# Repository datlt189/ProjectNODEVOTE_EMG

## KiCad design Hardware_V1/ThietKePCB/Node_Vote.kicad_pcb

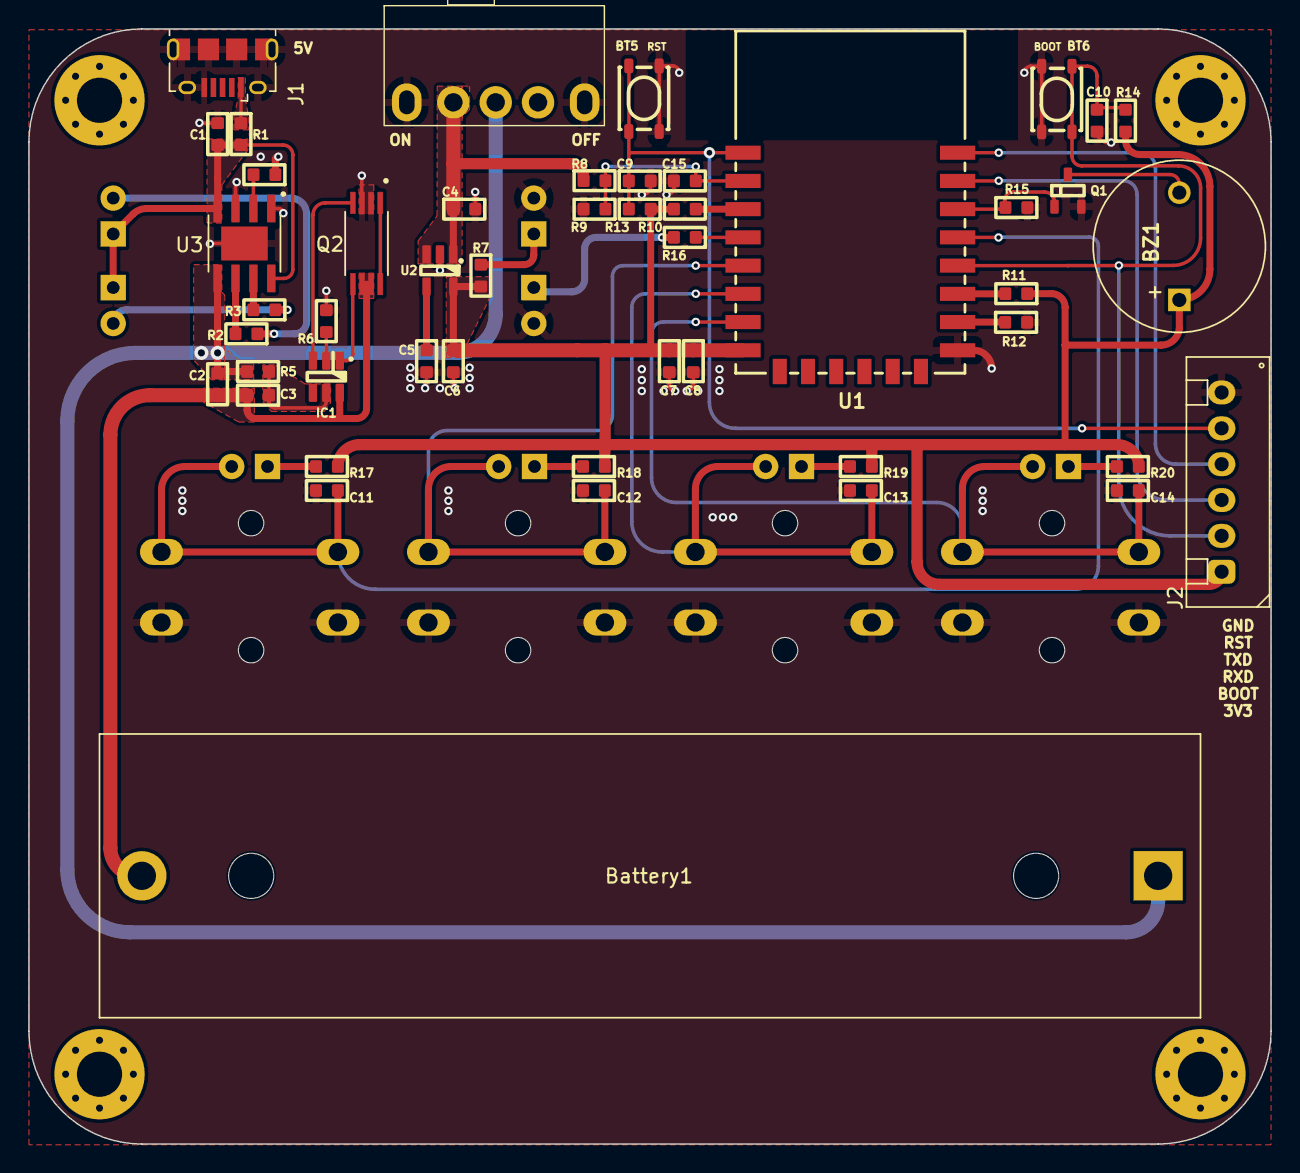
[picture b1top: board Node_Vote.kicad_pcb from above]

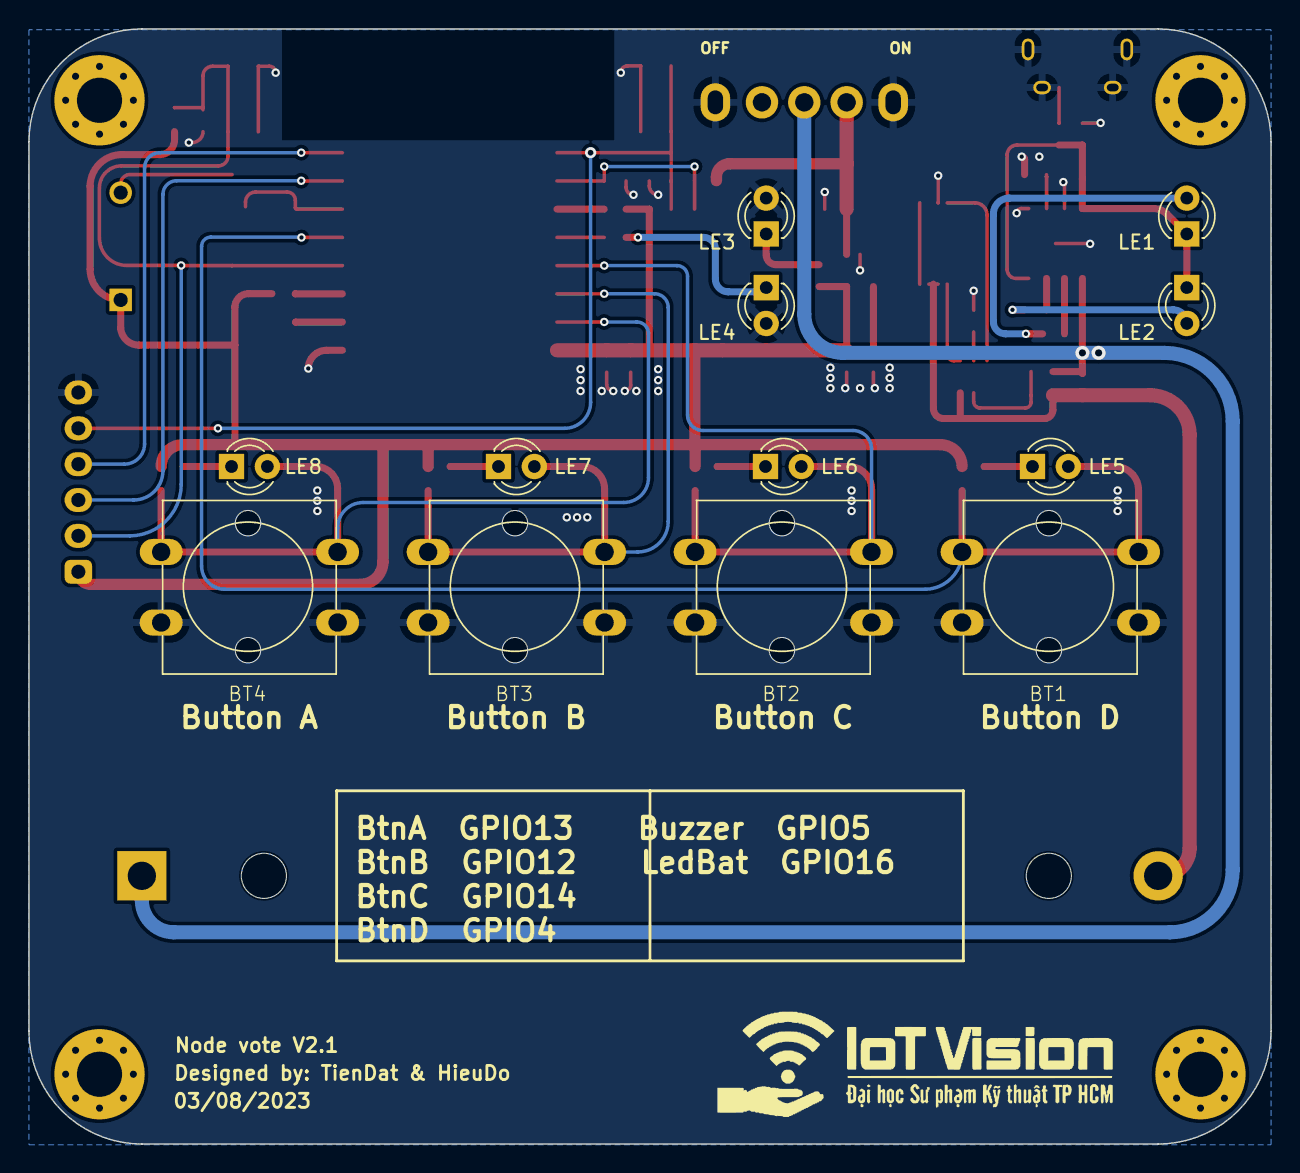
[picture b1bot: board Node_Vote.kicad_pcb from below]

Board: 2 copper layers, 88.0 x 79.0 mm, 60 parts (12 on the bottom side), 39 nets.

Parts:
BT1, BT2, BT3, BT4: SW_Push_B3F-4055_12x12x7.3_Omron; SW_Push_TactileSwitch_12x12mm_DIP
BT5, BT6: SW_Push_4.2x3.3x2.5_SMD; SW_SPST_PTS810
BZ1: 1206_DIP_Buzzer; Buzzer_12x6RM7.6
Battery1: Battery_Holder_1x18650_DIP; BatteryHolder_MPD_BH-18650-PC2
C1, C2: 10uF; C_0603
C3, C8, C9, C10, C11, C12, C13, C14, C15: 100nF; C_0603
C4, C6, C7: 1uF; C_0603
C5: 22nF; C_0603
IC1: DW01A; SOT23-6
J1: USB_B_Micro_5Ft_SMD_V1; USB_Micro-B
J2: XH_2.54_6P_Vertical; XH_6P_2.54mm_Vertical
LE1, LE5, LE6, LE7, LE8: Led_Green_3mm_DIP; LED_D3.0mm_Red
LE2, LE3: Led_Red_3mm_DIP; LED_D3.0mm_Red
LE4: Led_Blue_3mm_DIP; LED_D3.0mm_Red
Q1: N_Mosfet_SI2300; SOT23-3
Q2: FS8205A; TSSOP-8
R1: 0.5R; R_0603
R2, R3, R16, R17, R18, R19, R20: 1K5; R_0603
R4: 2K; R_0603
R5: 100R; R_0603
R6, R7, R9: 1K; R_0603
R8: 3k3; R_0603
R10, R11, R12, R13, R14: 10K; R_0603
R15: 1M; R_0603
S2: Slide_Switch_SS-12F23G6; SS-12F23G6
U1: ESP8266-ESP-12E; ESP8266-07__ESP32-C3-12F
U2: RT9193-33GB; SOT23-5
U3: TP4056

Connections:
+3V3: BZ1.1 (-), C6.1, C7.1, C8.1, J2.1, R7.2, R10.1, R11.1, R13.1, R14.1, R17.1, R18.1, R19.1, R20.1, U1.8 (VCC), U2.5 (VOUT)
/BUTTON/button.BTA: BT4.2, C14.1, LE8.2, U1.7 (GPIO13)
/BUTTON/button.BTB: BT3.2, C13.1, LE7.2, U1.6 (GPIO12)
/BUTTON/button.BTC: BT2.2, C12.1, LE6.2, U1.5 (GPIO14)
/BUTTON/button.BTD: BT1.2, C11.1, LE5.2, U1.19 (GPIO4)
/POWER/ADC_BAT: C4.1, R8.1, S2.1, U2.1 (VIN), U2.3 (EN)
/POWER/BAT+: Battery1.1 (+), C2.1, R5.1, S2.2, U3.5 (BAT)
/POWER/BAT-: Battery1.2 (-), C2.2, C3.2, IC1.6 (GND), Q2.6, Q2.7
/POWER/CHRG: R3.2, U3.7 (~CHRG)
/POWER/STDBY: R2.2, U3.6 (~STDBY)
/POWER/VBUS: C1.2, LE1.1, LE2.1, R1.2, U3.4 (VCC), U3.8 (CE)
/esp8266/ADC: C15.2, R8.2, R9.1, U1.2 (ADC)
/esp8266/BOOT: BT6.1, C10.1, J2.2, R14.2, U1.18 (GPIO0)
/esp8266/Buzzer: Q1.1 (G), R15.1, U1.20 (GPIO5)
/esp8266/EN: R10.2, U1.3 (EN)
/esp8266/GPIO2: R11.2, U1.17 (GPIO2)
/esp8266/Led_BAT: R16.1, U1.4 (GPIO16)
/esp8266/RST: BT5.1, C9.1, J2.5, R13.2, U1.1 (~RST)
/esp8266/RXD: J2.3, U1.21 (GPIO3/RXD)
/esp8266/TXD: J2.4, U1.22 (GPIO1/TXD)
GND: BT1.1, BT2.1, BT3.1, BT4.1, BT5.2, BT6.2, C1.1, C4.2, C5.2, C6.2, C7.2, C8.2, C9.2, C10.2, C11.2, C12.2, C13.2, C14.2, C15.1, J1.5 (GND), J1.6 (Shield), J2.6, LE3.2, LE4.2, Q1.2 (S), Q2.2, Q2.3, R4.1, R6.2, R9.2, R12.2, R15.2, S2.Shield, U1.15 (GND), U2.2 (GND), U3.1 (TEMP), U3.3 (GND), U3.9 (EP)
unnamed: BZ1.2 (+), Q1.3 (D)
unnamed: IC1.2 (CS), R6.1
unnamed: IC1.3 (OC), Q2.4
unnamed: IC1.1 (OD), Q2.5
unnamed: C3.1, IC1.5 (VCC), R5.2
unnamed: J1.1 (VBUS), R1.1
unnamed: LE1.2, R2.1
unnamed: LE2.2, R3.1
unnamed: LE3.1, R7.1
unnamed: LE4.1, R16.2
unnamed: LE5.1, R17.2
unnamed: LE6.1, R18.2
unnamed: LE7.1, R19.2
unnamed: LE8.1, R20.2
unnamed: Q2.1, Q2.8
unnamed: R12.1, U1.16 (GPIO15)
unnamed: C5.1, U2.4 (BP)
unnamed: R4.2, U3.2 (PROG)

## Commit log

2023-12-21 upload project
